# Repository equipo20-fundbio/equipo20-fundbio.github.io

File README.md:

## Welcome to GitHub Pages

You can use the [editor on GitHub](https://github.com/equipo20-fundbio/equipo20-fundbio.github.io/edit/master/README.md) to maintain and preview the content for your website in Markdown files.

Whenever you commit to this repository, GitHub Pages will run [Jekyll](https://jekyllrb.com/) to rebuild the pages in your site, from the content in your Markdown files.

### Markdown

Markdown is a lightweight and easy-to-use syntax for styling your writing. It includes conventions for

```markdown
Syntax highlighted code block

# Header 1
## Header 2
### Header 3

- Bulleted
- List

1. Numbered
2. List

**Bold** and _Italic_ and `Code` text

[Link](url) and 
```

For more details see [GitHub Flavored Markdown](https://guides.github.com/features/mastering-markdown/).

### Jekyll Themes

Your Pages site will use the layout and styles from the Jekyll theme you have selected in your [repository settings](https://github.com/equipo20-fundbio/equipo20-fundbio.github.io/settings). The name of this theme is saved in the Jekyll `_config.yml` configuration file.

### Support or Contact

Having trouble with Pages? Check out our [documentation](https://docs.github.com/categories/github-pages-basics/) or [contact support](https://github.com/contact) and we’ll help you sort it out.

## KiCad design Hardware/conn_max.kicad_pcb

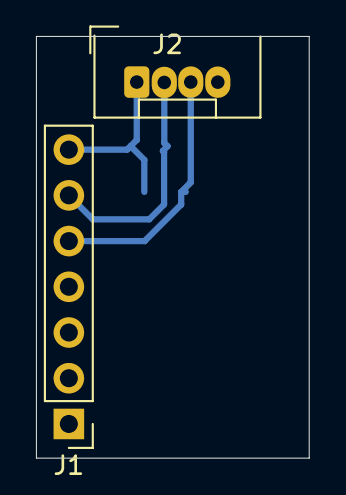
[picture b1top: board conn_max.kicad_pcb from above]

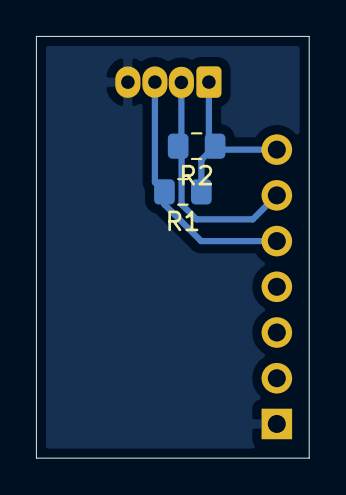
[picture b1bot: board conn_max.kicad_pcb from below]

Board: 2 copper layers, 15.2 x 23.4 mm, 4 parts (2 on the bottom side), 4 nets.

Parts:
J1: Conn_01x07_Female; PinHeader_1x07_P2.54mm_Vertical
J2: Conn_01x04_Female; JST_1x04_P1.50mm_tynko
R1, R2: R; R_0805_2012Metric_Pad1.15x1.40mm_HandSolder

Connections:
+3V3: J1.7, J2.1, R1.1, R2.1
GND: J1.1, J2.4
SCL: J1.6, J2.2, R2.2
SDA: J1.5, J2.3, R1.2

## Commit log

2020-09-03 Set theme jekyll-theme-cayman
